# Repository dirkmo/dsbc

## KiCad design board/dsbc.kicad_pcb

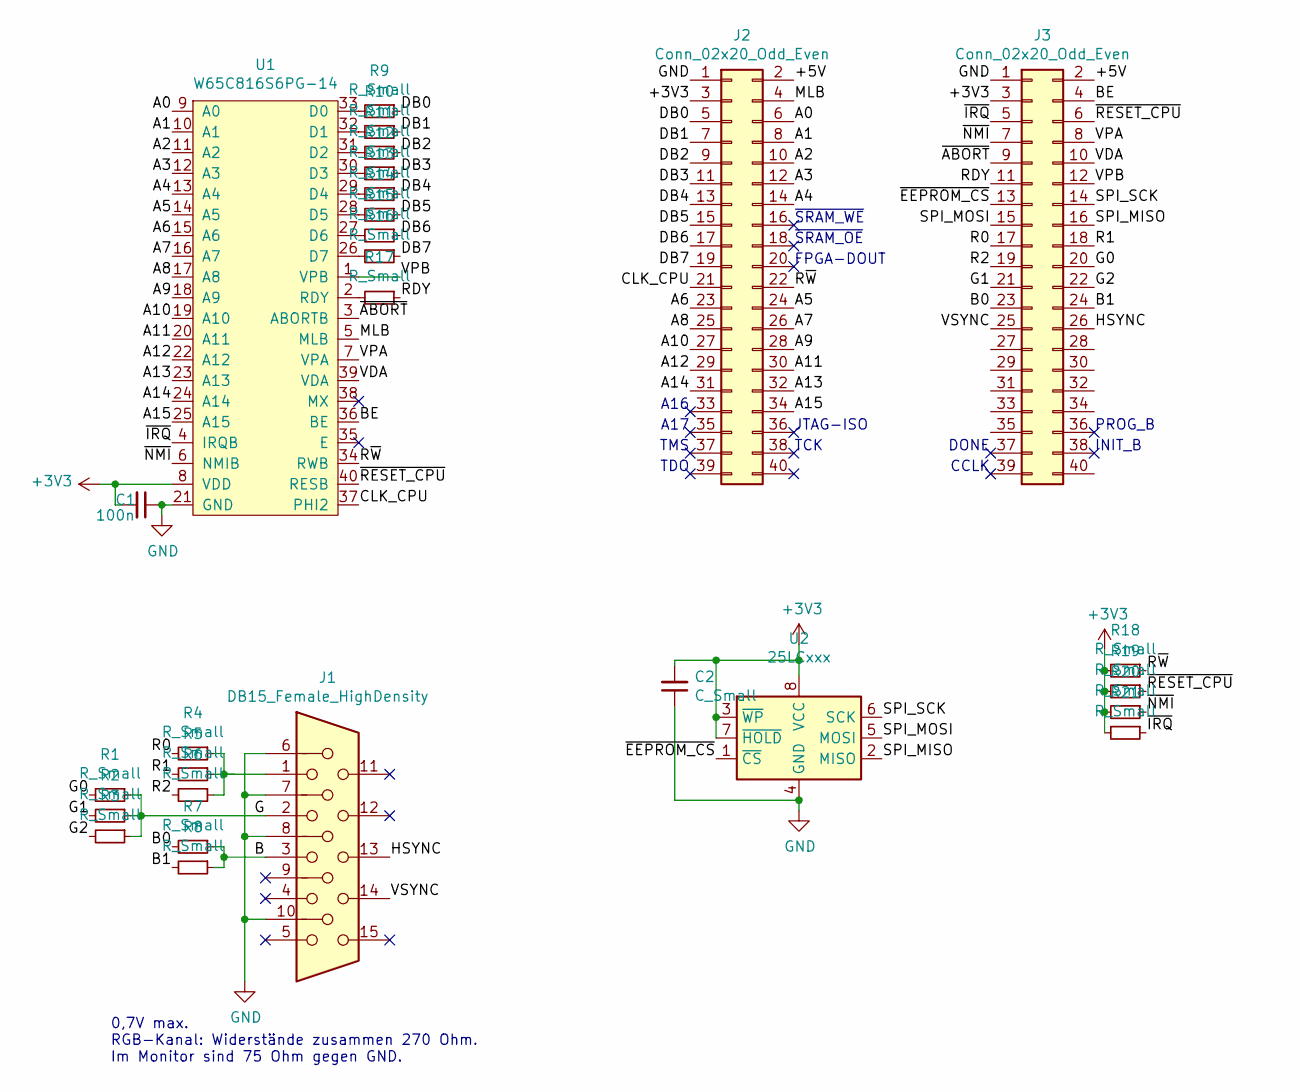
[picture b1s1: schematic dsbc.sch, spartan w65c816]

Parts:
C1: 100n; C_0805_2012Metric_Pad1.15x1.40mm_HandSolder
C2: C_Small; C_0805_2012Metric_Pad1.15x1.40mm_HandSolder
J1: DB15_Female_HighDensity; DSUB-15-HD_Female_Horizontal_P2.29x1.98mm_EdgePinOffset9.40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
J2, J3: Conn_02x20_Odd_Even; PinHeader_2x20_P2.54mm_Horizontal
R1, R2, R3, R4, R5, R6, R7, R8, R9, R10, R11, R12, R13, R14, R15, R16, R17, R18, R19, R20, R21: R_Small; R_0805_2012Metric_Pad1.15x1.40mm_HandSolder
U1: W65C816S6PG-14; DIP-40_W15.24mm
U2: 25LCxxx; DIP-8_W7.62mm_LongPads

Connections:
+3V3: C1.2, C2.2, J2.3, J3.3, R18.2, R19.2, R20.2, R21.2, U1.8 (VDD), U2.3 (~WP), U2.7 (~HOLD), U2.8 (VCC)
/+5V: J2.2, J3.2
/A0: J2.6, U1.9 (A0)
/A1: J2.8, U1.10 (A1)
/A2: J2.10, U1.11 (A2)
/A3: J2.12, U1.12 (A3)
/A4: J2.14, U1.13 (A4)
/A5: J2.24, U1.14 (A5)
/A6: J2.23, U1.15 (A6)
/A7: J2.26, U1.16 (A7)
/A8: J2.25, U1.17 (A8)
/A9: J2.28, U1.18 (A9)
/A10: J2.27, U1.19 (A10)
/A11: J2.30, U1.20 (A11)
/A12: J2.29, U1.22 (A12)
/A13: J2.32, U1.23 (A13)
/A14: J2.31, U1.24 (A14)
/A15: J2.34, U1.25 (A15)
/B: J1.3, R7.1, R8.1
/B0: J3.23, R7.2
/B1: J3.24, R8.2
/BE: J3.4, U1.36 (BE)
/CLK_CPU: J2.21, U1.37 (PHI2)
/DB0: J2.5, R9.1
/DB1: J2.7, R10.1
/DB2: J2.9, R11.1
/DB3: J2.11, R12.1
/DB4: J2.13, R13.1
/DB5: J2.15, R14.1
/DB6: J2.17, R15.1
/DB7: J2.19, R16.1
/G: J1.2, R1.1, R2.1, R3.1
/G0: J3.20, R1.2
/G1: J3.21, R2.2
/G2: J3.22, R3.2
/HSYNC: J1.13, J3.26
/MLB: J2.4, U1.5 (MLB)
/R0: J3.17, R4.2
/R1: J3.18, R5.2
/R2: J3.19, R6.2
/RDY: J3.11, R17.1
/R~W: J2.22, R18.1, U1.34 (RWB)
/SPI_MISO: J3.16, U2.2 (MISO)
/SPI_MOSI: J3.15, U2.5 (MOSI)
/SPI_SCK: J3.14, U2.6 (SCK)
/VDA: J3.10, U1.39 (VDA)
/VPA: J3.8, U1.7 (VPA)
/VPB: J3.12, U1.1 (VPB)
/VSYNC: J1.14, J3.25
/~ABORT: J3.9, U1.3 (ABORTB)
/~EEPROM_CS: J3.13, U2.1 (~CS)
/~IRQ: J3.5, R21.1, U1.4 (IRQB)
/~NMI: J3.7, R20.1, U1.6 (NMIB)
/~RESET_CPU: J3.6, R19.1, U1.40 (RESB)
GND: C1.1, C2.1, J1.6, J1.7, J1.8, J1.10, J2.1, J3.1, U1.21 (GND), U2.4 (GND)
unnamed: J1.1, R4.1, R5.1, R6.1
unnamed: R9.2, U1.33 (D0)
unnamed: R10.2, U1.32 (D1)
unnamed: R11.2, U1.31 (D2)
unnamed: R12.2, U1.30 (D3)
unnamed: R13.2, U1.29 (D4)
unnamed: R14.2, U1.28 (D5)
unnamed: R15.2, U1.27 (D6)
unnamed: R16.2, U1.26 (D7)
unnamed: R17.2, U1.2 (RDY)

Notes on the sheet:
~SRAM_WE
~SRAM_OE
A16
A17
TMS
TDO
JTAG-ISO
TCK
DONE
CCLK
PROG_B
INIT_B
FPGA-DOUT
0,7V max. RGB-Kanal: Widerstände zusammen 270 Ohm. Im Monitor sind 75 Ohm gegen GND.

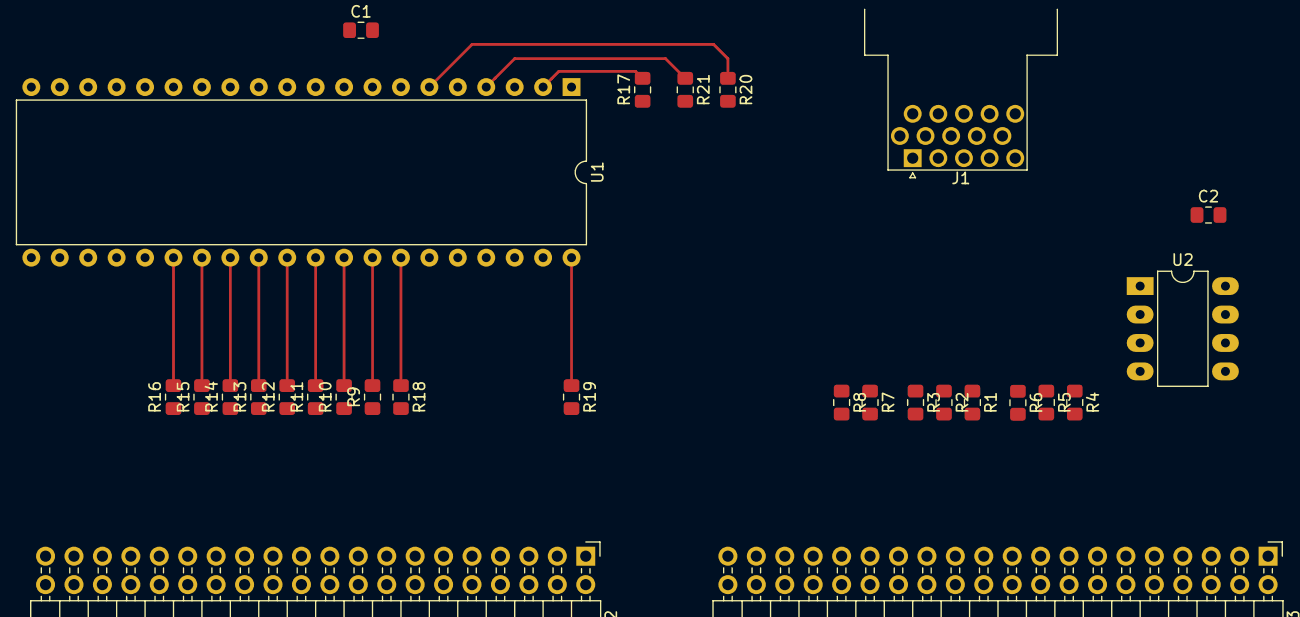
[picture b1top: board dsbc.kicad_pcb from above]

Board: 2 copper layers, 28 parts (0 on the bottom side), 65 nets.

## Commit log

2019-07-05 Initial
2019-07-05 add w65c816 symbol to lib
2019-07-05 add datasheet
2019-07-07 add 16mbit sram symbol
2019-07-07 added ps/2 connector
2019-07-07 add datasheets
2019-07-10 spartan branch
2019-07-10 uart wb bridge
2019-07-10 uart2wb work
2019-07-11 uart2wb bridge: syntax ok
2019-07-11 moving verilog code
2019-07-11 uart2wb: start verilator testbench
2019-07-12 uart2wb: basic tb writing works
2019-07-12 uart2wb: read work
2019-07-12 uart2wb: reset
2019-07-12 uart2wb: uart import
2019-07-15 schematic: add resistor to RDY pin
2019-07-15 sram2wb
2019-07-15 uart2wb: changing port rw to we
2019-07-15 top module
2019-07-15 create fpga project
2019-07-19 schematic: eeprom, resistors board: placement
2019-07-19 board: placement. pin headers have wrong orientation
2020-01-26 Teilweise neu geschrieben
2020-03-15 gelesene WB-Daten auf UART ausgeben
